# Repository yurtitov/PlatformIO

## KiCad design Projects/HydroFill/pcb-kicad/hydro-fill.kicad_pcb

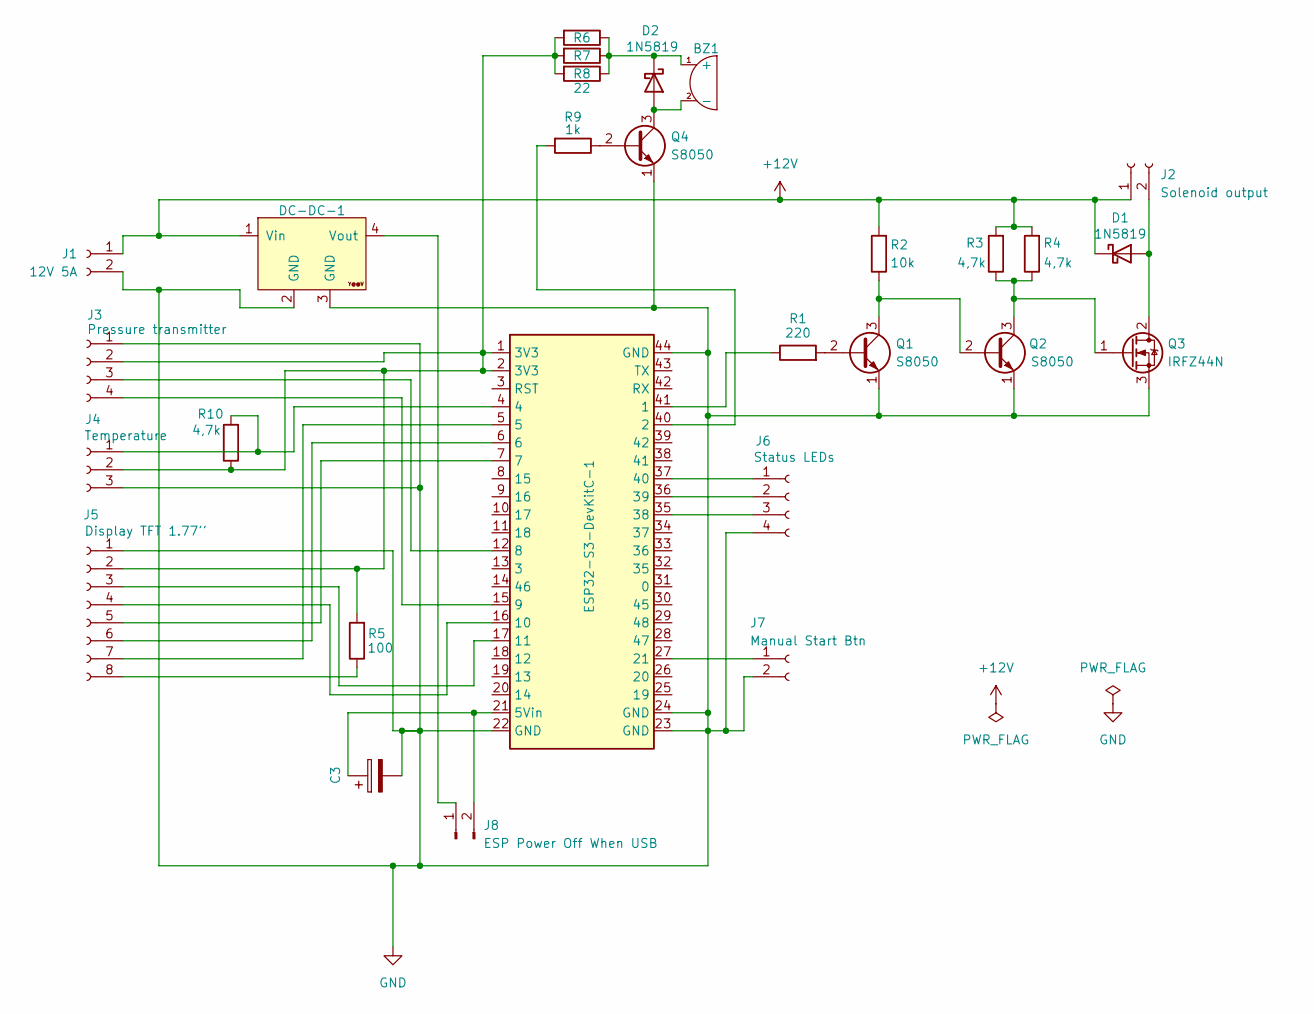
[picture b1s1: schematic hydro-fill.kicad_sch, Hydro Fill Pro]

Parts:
BZ1: Buzzer_12x9.5RM7.6
C3: 470uF 16V; CP_Radial_D8.0mm_P3.50mm
D1, D2: 1N5819; D_DO-41_SOD81_P10.16mm_Horizontal
DC-DC-1: YAAJ_DCDC_StepDown_LM2596; 1_DCDC_StepDown_LM2596
ESP32-S3-DevKitC-1: 1_ESP32-S3-DevKitC-1
J1: 12V 5A; JST_XH_B2B-XH-A_1x02_P2.50mm_Vertical
J2: Solenoid output; JST_XH_B2B-XH-A_1x02_P2.50mm_Vertical
J3: Pressure transmitter; JST_XH_B4B-XH-A_1x04_P2.50mm_Vertical
J4: Temperature; JST_XH_B3B-XH-A_1x03_P2.50mm_Vertical
J5: Display TFT 1.77''; PinHeader_1x08_P2.54mm_Vertical
J6: Status LEDs; PinHeader_1x04_P2.54mm_Vertical
J7: Manual Start Btn; JST_XH_B2B-XH-A_1x02_P2.50mm_Vertical
J8: ESP Power Off When USB
Q1, Q2, Q4: S8050; TO-92
Q3: IRFZ44N; TO-220-3_Vertical
R1: 220; R_Axial_DIN0204_L3.6mm_D1.6mm_P7.62mm_Horizontal
R2: 10k; R_Axial_DIN0204_L3.6mm_D1.6mm_P7.62mm_Horizontal
R3, R4, R10: 4,7k; R_Axial_DIN0204_L3.6mm_D1.6mm_P7.62mm_Horizontal
R5: 100; R_Axial_DIN0204_L3.6mm_D1.6mm_P7.62mm_Horizontal
R6, R7, R8: 22; R_Axial_DIN0204_L3.6mm_D1.6mm_P7.62mm_Horizontal
R9: 1k; R_Axial_DIN0204_L3.6mm_D1.6mm_P7.62mm_Horizontal

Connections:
+12V: D1.1 (K), DC-DC-1.1 (Vin), J1.1, J2.1, R2.2, R3.2, R4.2
GND: C3.2, DC-DC-1.2 (GND), DC-DC-1.3 (GND), ESP32-S3-DevKitC-1.22 (GND), ESP32-S3-DevKitC-1.23 (GND), ESP32-S3-DevKitC-1.24 (GND), ESP32-S3-DevKitC-1.44 (GND), J1.2, J3.1, J4.3, J5.1, J6.4, J7.2, Q1.1 (E), Q2.1 (E), Q3.3 (S), Q4.1 (E)
unnamed: BZ1.1 (+), D2.1 (K), R6.1, R7.1, R8.1
unnamed: BZ1.2 (-), D2.2 (A), Q4.3 (C)
unnamed: D1.2 (A), J2.2, Q3.2 (D)
unnamed: DC-DC-1.4 (Vout), J8.1
unnamed: ESP32-S3-DevKitC-1.41 (1), R1.1
unnamed: ESP32-S3-DevKitC-1.40 (2), R9.2
unnamed: C3.1, ESP32-S3-DevKitC-1.21 (5Vin), J8.2
unnamed: ESP32-S3-DevKitC-1.12 (8), J3.3
unnamed: ESP32-S3-DevKitC-1.15 (9), J3.4
unnamed: ESP32-S3-DevKitC-1.16 (10), J5.4
unnamed: ESP32-S3-DevKitC-1.17 (11), J5.3
unnamed: ESP32-S3-DevKitC-1.27 (21), J7.1
unnamed: ESP32-S3-DevKitC-1.35 (38), J6.3
unnamed: ESP32-S3-DevKitC-1.36 (39), J6.2
unnamed: ESP32-S3-DevKitC-1.37 (40), J6.1
unnamed: ESP32-S3-DevKitC-1.1 (3V3), ESP32-S3-DevKitC-1.2 (3V3), J3.2, J4.2, J5.2, R5.2, R6.2, R7.2, R8.2, R10.1
unnamed: ESP32-S3-DevKitC-1.4, J4.1, R10.2
unnamed: ESP32-S3-DevKitC-1.7, J5.5
unnamed: ESP32-S3-DevKitC-1.6, J5.6
unnamed: ESP32-S3-DevKitC-1.5, J5.7
unnamed: J5.8, R5.1
unnamed: Q1.2 (B), R1.2
unnamed: Q1.3 (C), Q2.2 (B), R2.1
unnamed: Q2.3 (C), Q3.1 (G), R3.1, R4.1
unnamed: Q4.2 (B), R9.1

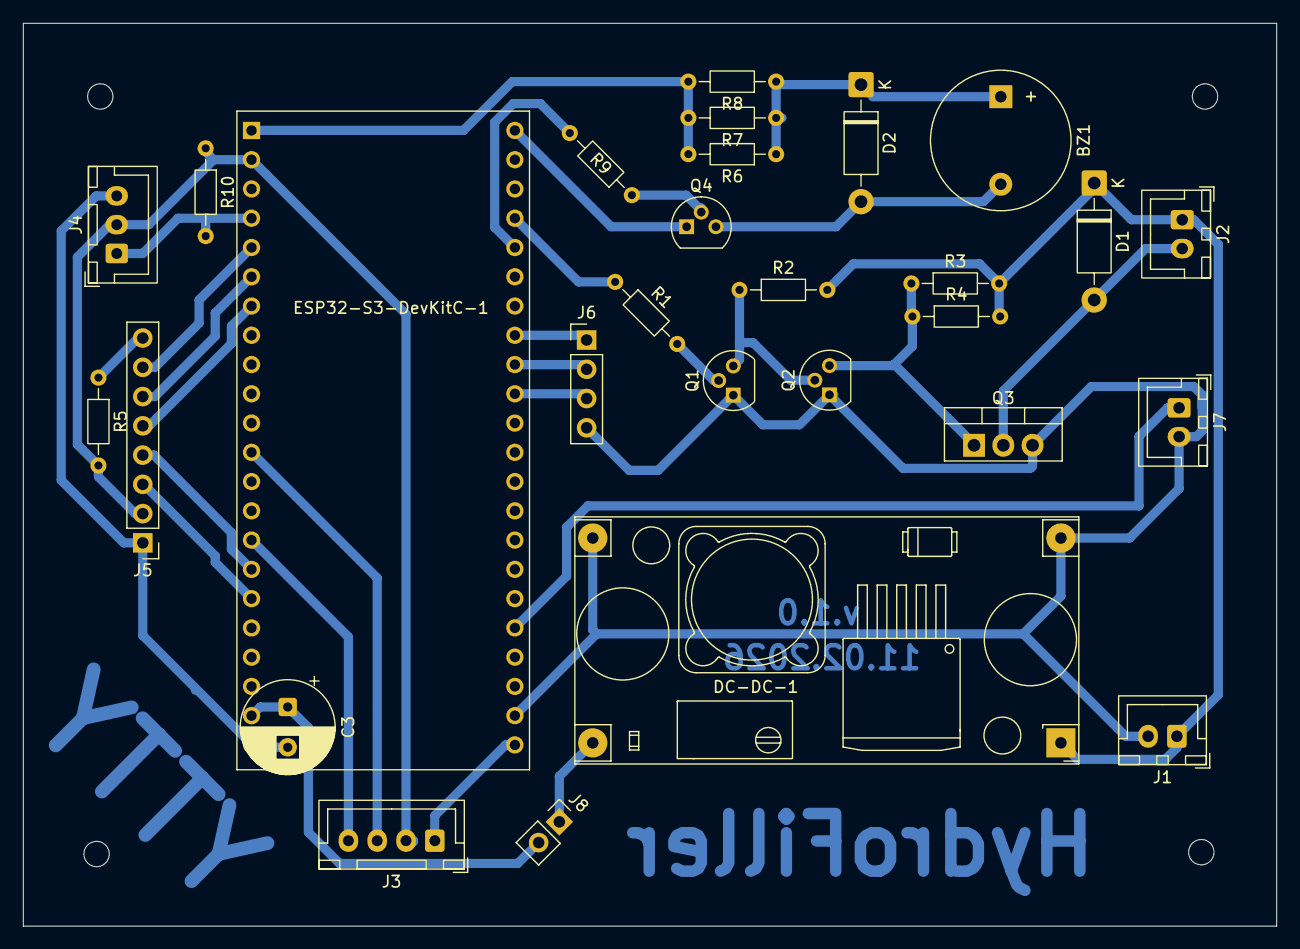
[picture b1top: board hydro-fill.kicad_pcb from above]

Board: 2 copper layers, 108.8 x 78.4 mm, 28 parts (0 on the bottom side), 27 nets.

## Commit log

2026-02-01 Add led-matrix-test project
2026-02-01 Start HedroFill DIY project
2026-02-01 [HydroFill] Add config.json for configuration
2026-02-01 [HydroFill] Add PressureSensor logic
2026-02-01 [HydroFill] Add multi threading for PressureSensor
2026-02-15 Setup HydroFiller board: - Add I2CScanner - Setup 1.77 TFT display - Setup buzzer - Setup LEDs - Setup solenoid valve
2026-02-16 [HydroFill] Encapsulate display logic to the appropriate class
2026-02-16 [HydroFill] Add PCB KiCAD
2026-02-16 [HydroFill] Encapsulate pressure sensor logic to the appropriate class
2026-02-17 [HydroFiller][PCB] Add `ESP Power Of When USB connected` connector
    - Remove 1000mF capacitor
2026-02-17 [HydroFiller][PCB] Add resistor 4.7kOm to out of temperature sensor
2026-02-17 [HydroFiller] Implement TemperatureSensor logic
2026-02-19 [HydroFiller] Rotate display view
2026-02-19 [HydroFiller] Implement LEDSintalManager
2026-02-19 [HydroFiller] WIP. Implement RefillSystem FSM
2026-02-21 [HydroFiller] Add ButtonManager
2026-02-21 [HydroFiller] Fix multi threading in PressureSensor
